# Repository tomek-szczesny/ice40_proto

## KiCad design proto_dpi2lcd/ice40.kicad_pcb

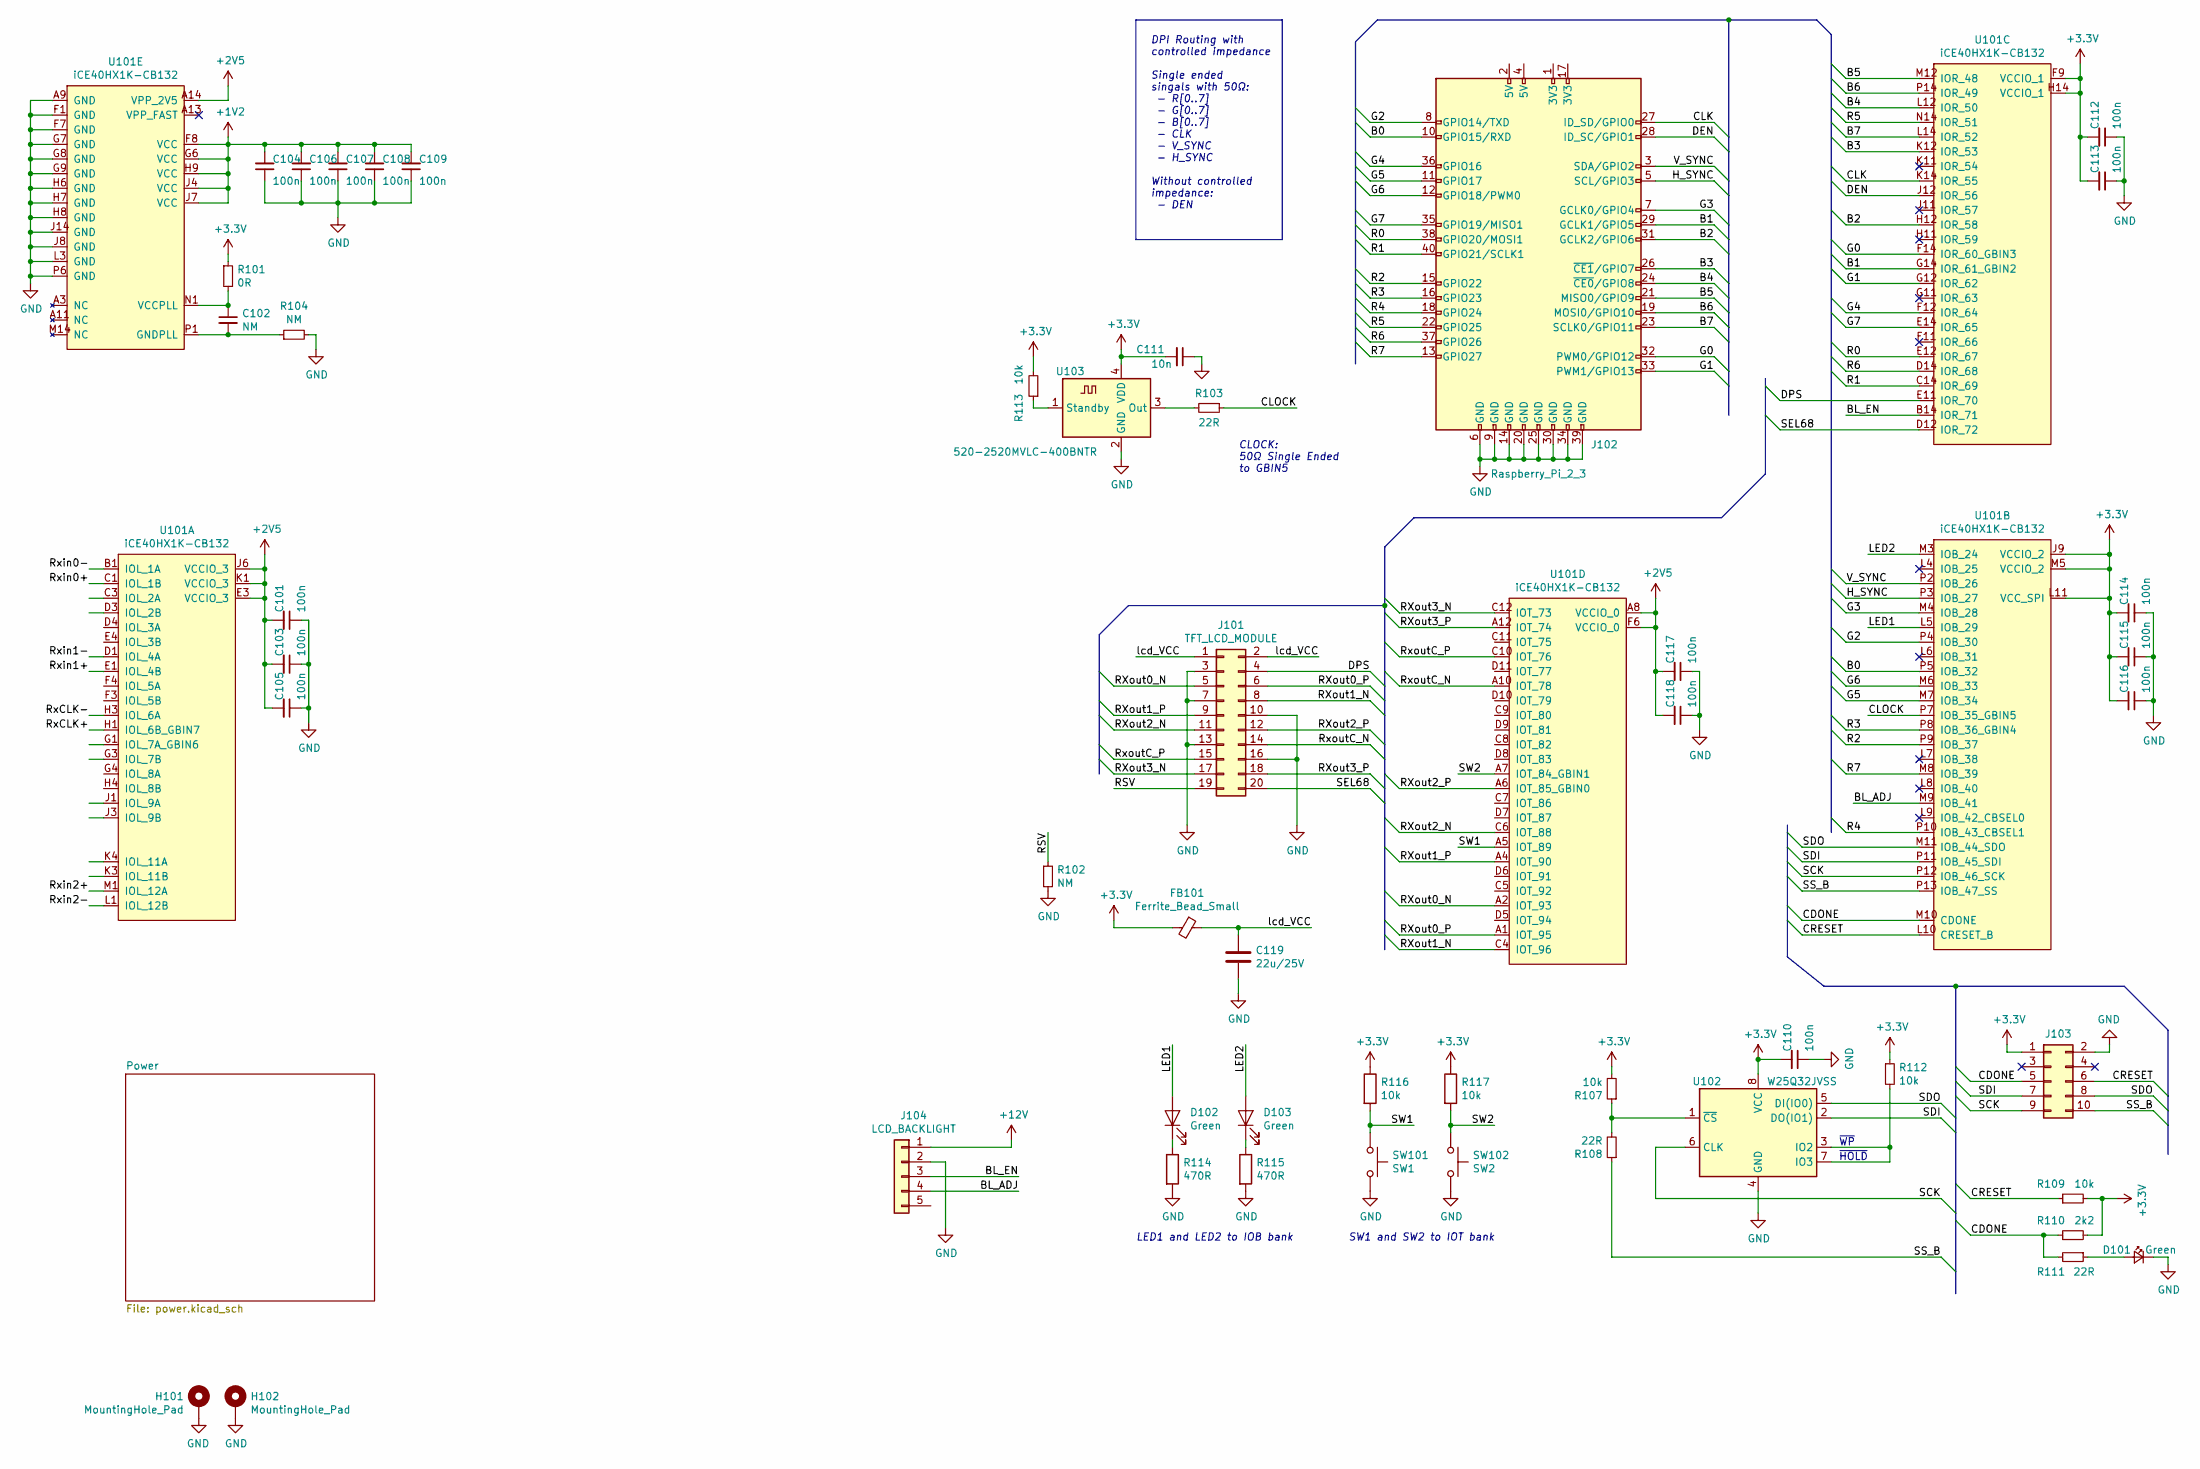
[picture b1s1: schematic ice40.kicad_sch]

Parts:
C101, C103, C104, C105, C106, C107, C108, C109: 100n; C_0402_1005Metric
C102: NM; C_0603_1608Metric
C110, C112, C113, C114, C115, C116, C117, C118: 100n; C_0603_1608Metric
C111: 10n; C_0603_1608Metric
C119: 22u/25V; C_1210_3225Metric
D101: Green; LED_0603_1608Metric
D102, D103: Green; D_0805_2012Metric
FB101: Ferrite_Bead_Small; L_1210_3225Metric_Pad1.42x2.65mm_HandSolder
H101, H102: MountingHole_Pad; MountingHole_3.2mm_M3_Pad_Via
J101: TFT_LCD_MODULE; IDC-Header_2x10_P2.54mm_Vertical
J102: Raspberry_Pi_2_3; IDC-Header_2x20_P2.54mm_Vertical
J103: Conn_02x05_Odd_Even; PinSocket_2x05_P2.54mm_Vertical
J104: LCD_BACKLIGHT; PinHeader_1x05_P2.54mm_Vertical
R101: 0R; R_0603_1608Metric
R102, R104: NM; R_0603_1608Metric
R103, R108, R111: 22R; R_0603_1608Metric
R107, R109, R112, R113, R116, R117: 10k; R_0603_1608Metric
R110: 2k2; R_0603_1608Metric
R114, R115: 470R; R_0603_1608Metric
SW101: SW1; SW_PUSH_6mm_H4.3mm
SW102: SW2; SW_PUSH_6mm_H4.3mm
U101: iCE40HX1K-CB132; Lattice_csBGA-132_Option2
U102: W25Q32JVSS; SOIC-8_5.23x5.23mm_P1.27mm
U103: 520-2520MVLC-400BNTR; Oscillator_SMD_Abracon_ASDMB-4Pin_2.5x2.0mm

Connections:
+1V2: C104.2, C106.2, C107.2, C108.2, C109.2, U101.F8 (VCC), U101.G6 (VCC), U101.H9 (VCC), U101.J4 (VCC), U101.J7 (VCC); also elsewhere on the board
+2V5: C101.2, C103.2, C105.2, C117.2, C118.2, U101.A8 (VCCIO_0), U101.A14 (VPP_2V5), U101.E3 (VCCIO_3), U101.F6 (VCCIO_0), U101.J6 (VCCIO_3), U101.K1 (VCCIO_3); also elsewhere on the board
+3V3: C110.2, C111.2, C112.2, C113.2, C114.2, C115.2, C116.2, FB101.2, J103.1, R101.1, R107.2, R109.2, R110.2, R112.1, R113.2, R116.1, R117.1, U101.F9 (VCCIO_1), U101.H14 (VCCIO_1), U101.J9 (VCCIO_2), U101.L11 (VCC_SPI), U101.M5 (VCCIO_2), U102.8 (VCC), U103.4 (VDD); also elsewhere on the board
+12V: J104.1; also elsewhere on the board
/B0: J102.10 (GPIO15/RXD), U101.P5 (IOB_32)
/B1: J102.29 (GCLK1/GPIO5), U101.G14 (IOR_61_GBIN2)
/B2: J102.31 (GCLK2/GPIO6), U101.H12 (IOR_58)
/B3: J102.26 (~CE1/GPIO7), U101.K12 (IOR_53)
/B4: J102.24 (~CE0/GPIO8), U101.L12 (IOR_50)
/B5: J102.21 (MISO0/GPIO9), U101.M12 (IOR_48)
/B6: J102.19 (MOSI0/GPIO10), U101.P14 (IOR_49)
/B7: J102.23 (SCLK0/GPIO11), U101.L14 (IOR_52)
/BL_ADJ: J104.4, U101.M9 (IOB_41)
/BL_EN: J104.3, U101.B14 (IOR_71)
/CDONE: J103.5, R110.1, R111.2, U101.M10 (CDONE)
/CLK: J102.27 (ID_SD/GPIO0), U101.K14 (IOR_55)
/CLOCK: R103.1, U101.P7 (IOB_35_GBIN5)
/CRESET: J103.6, R109.1, U101.L10 (CRESET_B)
/DEN: J102.28 (ID_SC/GPIO1), U101.J12 (IOR_56)
/DPS: J101.4, U101.E11 (IOR_70)
/G0: J102.32 (PWM0/GPIO12), U101.F14 (IOR_60_GBIN3)
/G1: J102.33 (PWM1/GPIO13), U101.G12 (IOR_62)
/G2: J102.8 (GPIO14/TXD), U101.P4 (IOB_30)
/G3: J102.7 (GCLK0/GPIO4), U101.M4 (IOB_28)
/G4: J102.36 (GPIO16), U101.F12 (IOR_64)
/G5: J102.11 (GPIO17), U101.M7 (IOB_34)
/G6: J102.12 (GPIO18/PWM0), U101.M6 (IOB_33)
/G7: J102.35 (GPIO19/MISO1), U101.E14 (IOR_65)
/H_SYNC: J102.5 (SCL/GPIO3), U101.P3 (IOB_27)
/LED1: D102.2 (A), U101.L5 (IOB_29)
/LED2: D103.2 (A), U101.M3 (IOB_24)
/R0: J102.38 (GPIO20/MOSI1), U101.E12 (IOR_67)
/R1: J102.40 (GPIO21/SCLK1), U101.C14 (IOR_69)
/R2: J102.15 (GPIO22), U101.P9 (IOB_37)
/R3: J102.16 (GPIO23), U101.P8 (IOB_36_GBIN4)
/R4: J102.18 (GPIO24), U101.P10 (IOB_43_CBSEL1)
/R5: J102.22 (GPIO25), U101.N14 (IOR_51)
/R6: J102.37 (GPIO26), U101.D14 (IOR_68)
/R7: J102.13 (GPIO27), U101.M8 (IOB_39)
/RSV: J101.19, R102.1
/RXout0_N: J101.5, U101.A2 (IOT_93)
/RXout0_P: J101.6, U101.A1 (IOT_95)
/RXout1_N: J101.8, U101.C4 (IOT_96)
/RXout1_P: J101.9, U101.A4 (IOT_90)
/RXout2_N: J101.11, U101.C6 (IOT_88)
/RXout2_P: J101.12, U101.A6 (IOT_85_GBIN0)
/RXout3_N: J101.17, U101.C12 (IOT_73)
/RXout3_P: J101.18, U101.A12 (IOT_74)
/RxCLK+: U101.H1 (IOL_6B_GBIN7)
/RxCLK-: U101.H3 (IOL_6A)
/Rxin0+: U101.C1 (IOL_1B)
/Rxin0-: U101.B1 (IOL_1A)
/Rxin1+: U101.E1 (IOL_4B)
/Rxin1-: U101.D1 (IOL_4A)
/Rxin2+: U101.M1 (IOL_12A)
/Rxin2-: U101.L1 (IOL_12B)
/RxoutC_N: J101.14, U101.A10 (IOT_78)
/RxoutC_P: J101.15, U101.C10 (IOT_76)
/SCK: J103.9, U101.P12 (IOB_46_SCK), U102.6 (CLK)
/SDI: J103.7, U101.P11 (IOB_45_SDI), U102.2 (DO(IO1))
/SDO: J103.8, U101.M11 (IOB_44_SDO), U102.5 (DI(IO0))
/SEL68: J101.20, U101.D12 (IOR_72)
/SS_B: J103.10, R108.1, U101.P13 (IOB_47_SS)
/SW1: R116.2, SW101.1, U101.A5 (IOT_89)
/SW2: R117.2, SW102.1, U101.A7 (IOT_84_GBIN1)
/V_SYNC: J102.3 (SDA/GPIO2), U101.P2 (IOB_26)
/lcd_VCC: C119.1, FB101.1, J101.1, J101.2
unnamed: C102.1, R101.2, U101.N1 (VCCPLL)
unnamed: C102.2, R104.1, U101.P1 (GNDPLL)
unnamed: D101.2 (A), R111.1
unnamed: D102.1 (K), R114.1
unnamed: D103.1 (K), R115.1
unnamed: R103.2, U103.3 (Out)
unnamed: R107.1, R108.2, U102.1 (~CS)
unnamed: R112.2, U102.3 (IO2), U102.7 (IO3)
unnamed: R113.1, U103.1 (Standby)

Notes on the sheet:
~{HOLD}
~{WP}
LED1 and LED2 to IOB bank
SW1 and SW2 to IOT bank
CLOCK: 50Ω Single Ended to GBIN5
DPI Routing with controlled impedance Single ended singals with 50Ω: - R[0..7] - G[0..7] - B[0..7] - CLK - V_SYNC - H_SYNC Without controlled impedance: - DEN

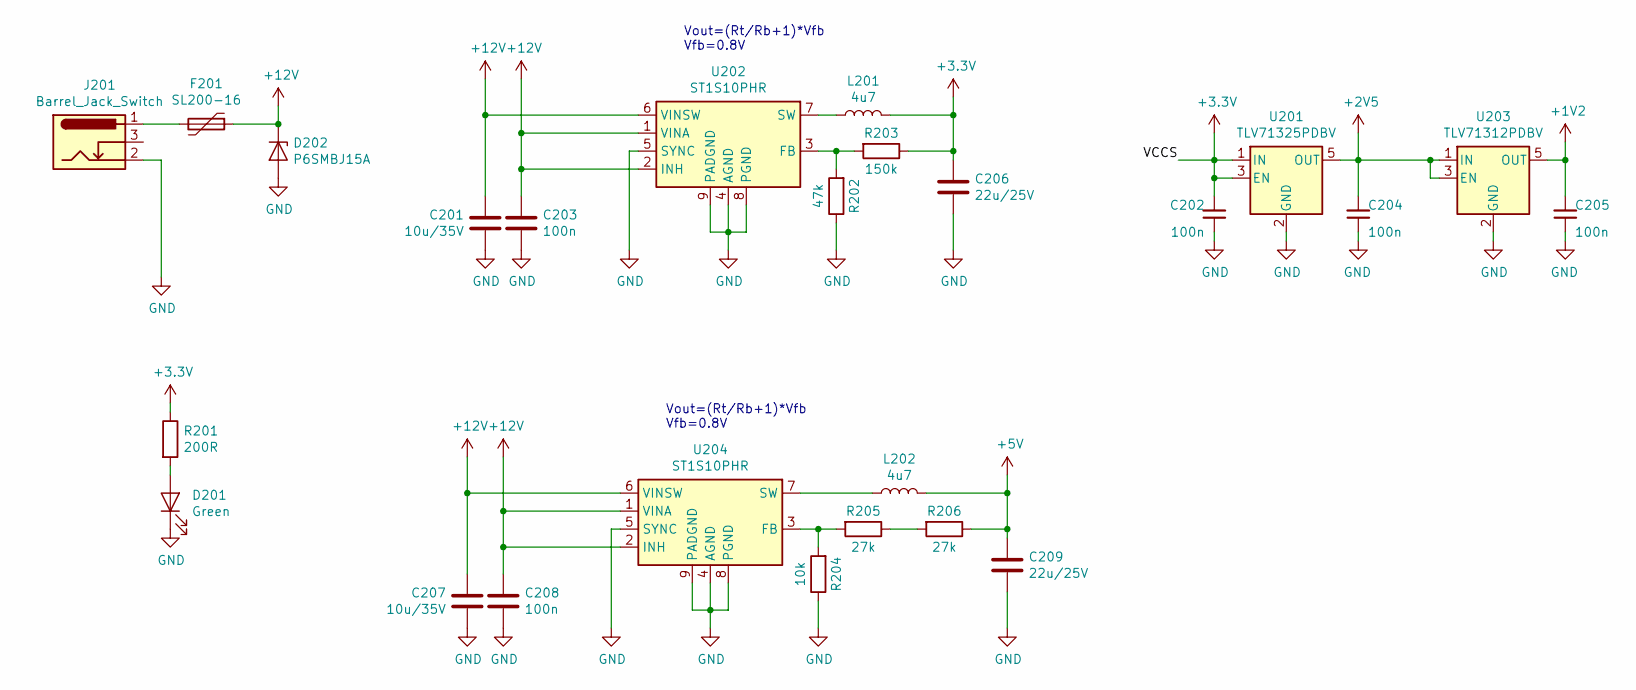
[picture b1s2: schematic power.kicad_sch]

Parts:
C201, C207: 10u/35V; C_1210_3225Metric
C202, C203, C204, C205, C208: 100n; C_0603_1608Metric
C206, C209: 22u/25V; C_1210_3225Metric
D201: Green; D_0805_2012Metric
D202: P6SMBJ15A; D_SMB
F201: SL200-16; Fuse_2920_7451Metric_Pad2.10x5.45mm_HandSolder
J201: Barrel_Jack_Switch; BarrelJack_Horizontal
L201, L202: 4u7; L_12x12mm_H8mm
R201: 200R; R_0603_1608Metric
R202: 47k; R_0603_1608Metric
R203: 150k; R_0603_1608Metric
R204: 10k; R_0603_1608Metric
R205, R206: 27k; R_0603_1608Metric
U201: TLV71325PDBV; SOT-23-5
U202, U204: ST1S10PHR; TI_SO-PowerPAD-8
U203: TLV71312PDBV; SOT-23-5

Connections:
+1V2: C205.2, U203.5 (OUT); also elsewhere on the board
+2V5: C204.2, U201.5 (OUT), U203.1 (IN), U203.3 (EN); also elsewhere on the board
+3V3: C202.2, C206.1, L201.2, R201.1, R203.1, U201.1 (IN), U201.3 (EN); also elsewhere on the board
+5V: C209.1, L202.2, R206.1
+12V: C201.2, C203.1, C207.2, C208.1, D202.1 (K), F201.1, U202.1 (VINA), U202.2 (INH), U202.6 (VINSW), U204.1 (VINA), U204.2 (INH), U204.6 (VINSW); also elsewhere on the board
unnamed: D201.2 (A), R201.2
unnamed: F201.2, J201.1
unnamed: L201.1, U202.7 (SW)
unnamed: L202.1, U204.7 (SW)
unnamed: R202.2, R203.2, U202.3 (FB)
unnamed: R204.2, R205.2, U204.3 (FB)
unnamed: R205.1, R206.2

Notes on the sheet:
Vout=(Rt/Rb+1)*Vfb Vfb=0.8V

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
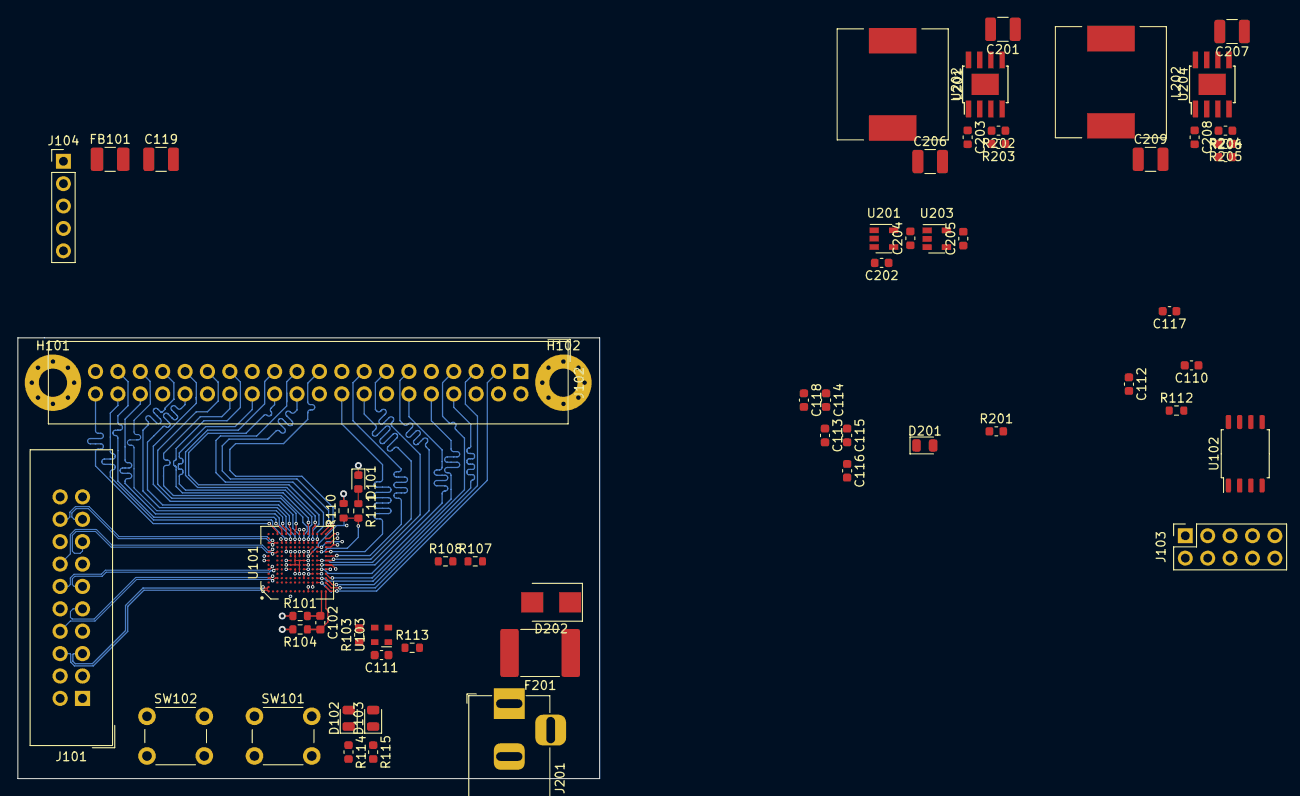
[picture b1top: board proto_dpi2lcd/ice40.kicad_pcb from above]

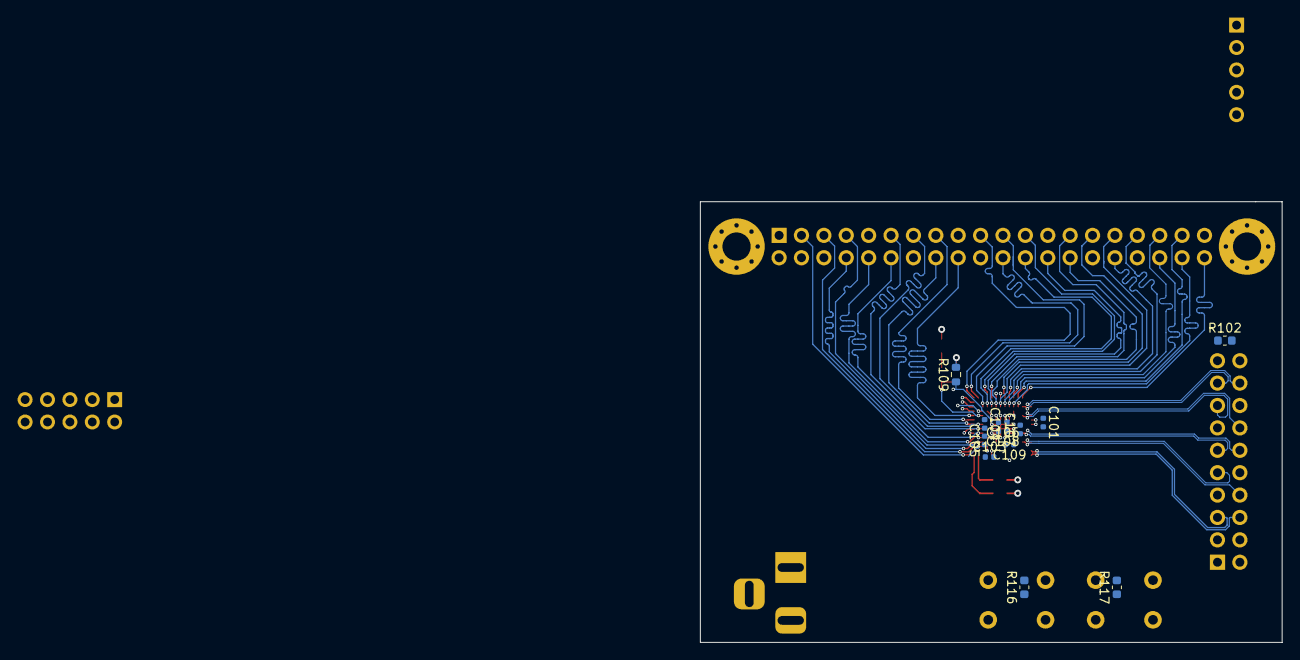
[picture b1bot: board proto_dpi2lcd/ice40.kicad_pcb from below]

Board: 4 copper layers, 66.0 x 50.0 mm, 74 parts (12 on the bottom side), 77 nets.

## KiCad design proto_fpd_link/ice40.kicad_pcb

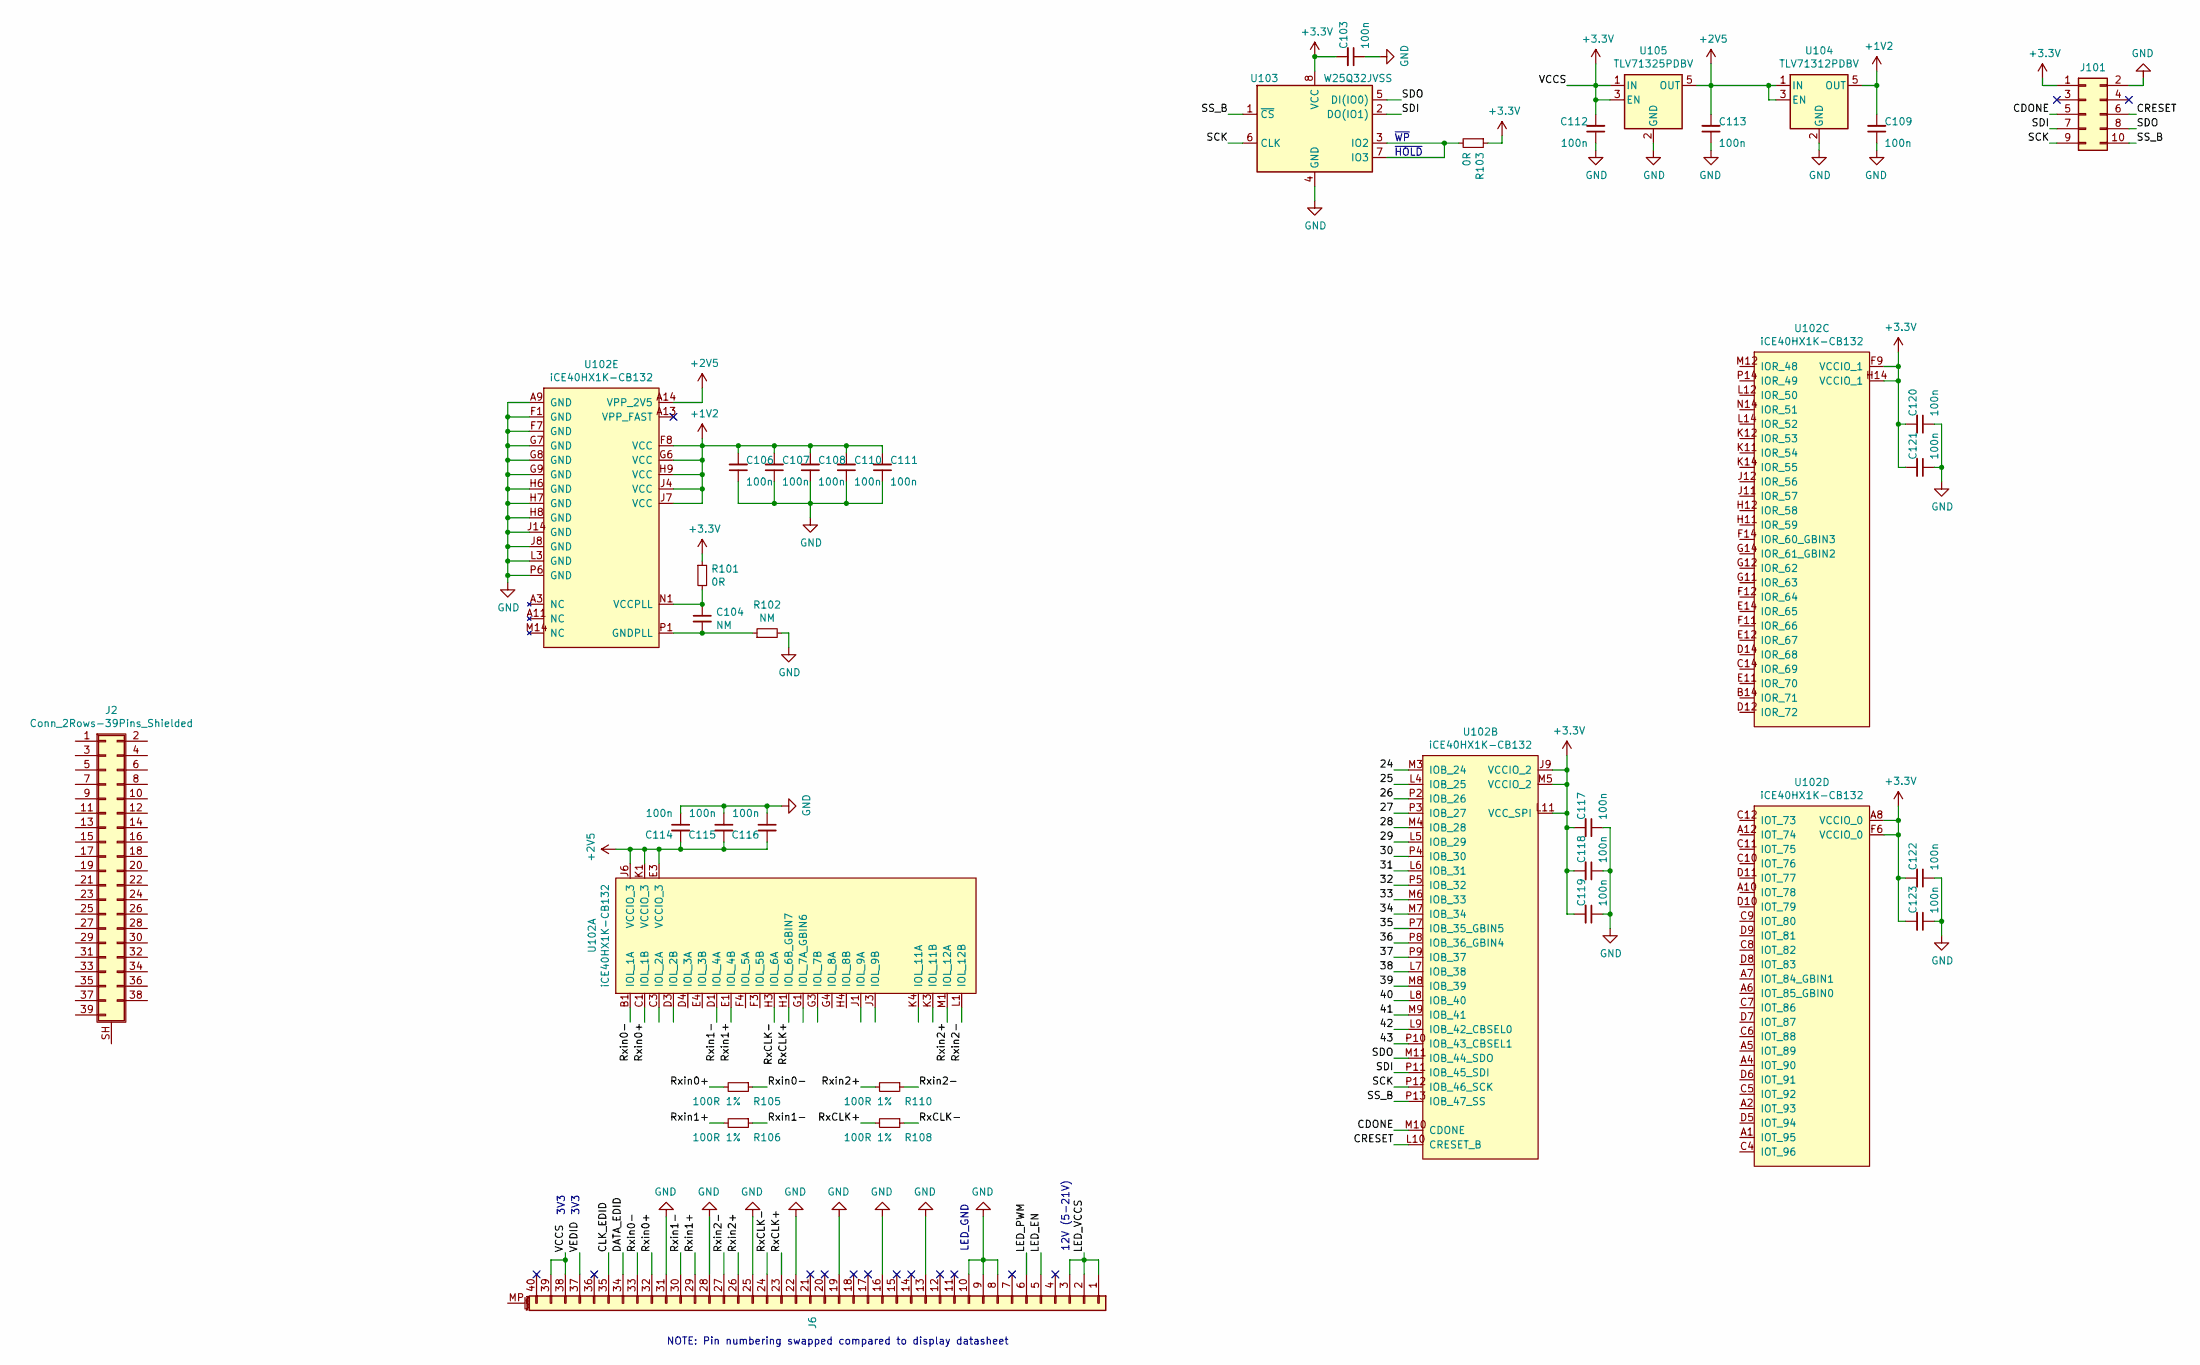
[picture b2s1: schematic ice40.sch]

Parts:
C103, C106, C107, C108, C109, C110, C111, C112, C113, C114, C115, C116, C117, C118, C119, C120, C121, C122, C123: 100n; C_0603_1608Metric
C104: NM; C_0603_1608Metric
J2: Conn_2Rows-39Pins_Shielded
J6: Conn_01x40_MountingPin; Hirose_FH12-40S-0.5SH_1x40-1MP_P0.50mm_Horizontal
J101: Conn_02x05_Odd_Even; PinSocket_2x05_P2.54mm_Vertical
R101, R103: 0R; R_0603_1608Metric
R102: NM; R_0603_1608Metric
R105, R106, R108, R110: 100R 1%; R_0402_1005Metric
U102: iCE40HX1K-CB132; Lattice_csBGA-132_Option2
U103: W25Q32JVSS; SOIC-8_5.23x5.23mm_P1.27mm
U104: TLV71312PDBV; SOT-23-5
U105: TLV71325PDBV; SOT-23-5

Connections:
+1V2: C106.2, C107.2, C108.2, C109.2, C110.2, C111.2, U102.F8 (VCC), U102.G6 (VCC), U102.H9 (VCC), U102.J4 (VCC), U102.J7 (VCC), U104.5 (OUT)
+2V5: C113.2, C114.2, C115.2, C116.2, U102.A14 (VPP_2V5), U102.E3 (VCCIO_3), U102.J6 (VCCIO_3), U102.K1 (VCCIO_3), U104.1 (IN), U104.3 (EN), U105.5 (OUT)
+3V3: C103.2, C112.2, C117.2, C118.2, C119.2, C120.2, C121.2, C122.2, C123.2, J6.38, J6.39, J101.1, R101.1, R103.1, U102.A8 (VCCIO_0), U102.F6 (VCCIO_0), U102.F9 (VCCIO_1), U102.H14 (VCCIO_1), U102.J9 (VCCIO_2), U102.L11 (VCC_SPI), U102.M5 (VCCIO_2), U103.8 (VCC), U105.1 (IN), U105.3 (EN)
/24: U102.M3 (IOB_24)
/25: U102.L4 (IOB_25)
/26: U102.P2 (IOB_26)
/27: U102.P3 (IOB_27)
/28: U102.M4 (IOB_28)
/29: U102.L5 (IOB_29)
/30: U102.P4 (IOB_30)
/31: U102.L6 (IOB_31)
/32: U102.P5 (IOB_32)
/33: U102.M6 (IOB_33)
/34: U102.M7 (IOB_34)
/35: U102.P7 (IOB_35_GBIN5)
/36: U102.P8 (IOB_36_GBIN4)
/37: U102.P9 (IOB_37)
/38: U102.L7 (IOB_38)
/39: U102.M8 (IOB_39)
/40: U102.L8 (IOB_40)
/41: U102.M9 (IOB_41)
/42: U102.L9 (IOB_42_CBSEL0)
/43: U102.P10 (IOB_43_CBSEL1)
/CDONE: J101.5, U102.M10 (CDONE)
/CLK_EDID: J6.35
/CRESET: J101.6, U102.L10 (CRESET_B)
/DATA_EDID: J6.34
/LED_EN: J6.5
/LED_PWM: J6.6
/LED_VCCS: J6.1, J6.2, J6.3
/RxCLK+: J6.23, R108.2, U102.H1 (IOL_6B_GBIN7)
/RxCLK-: J6.24, R108.1, U102.H3 (IOL_6A)
/Rxin0+: J6.32, R105.2, U102.C1 (IOL_1B)
/Rxin0-: J6.33, R105.1, U102.B1 (IOL_1A)
/Rxin1+: J6.29, R106.2, U102.E1 (IOL_4B)
/Rxin1-: J6.30, R106.1, U102.D1 (IOL_4A)
/Rxin2+: J6.26, R110.2, U102.M1 (IOL_12A)
/Rxin2-: J6.27, R110.1, U102.L1 (IOL_12B)
/SCK: J101.9, U102.P12 (IOB_46_SCK), U103.6 (CLK)
/SDI: J101.7, U102.P11 (IOB_45_SDI), U103.2 (DO(IO1))
/SDO: J101.8, U102.M11 (IOB_44_SDO), U103.5 (DI(IO0))
/SS_B: J101.10, U102.P13 (IOB_47_SS), U103.1 (~CS)
/VEDID: J6.37
GND: C103.1, C106.1, C107.1, C108.1, C109.1, C110.1, C111.1, C112.1, C113.1, C114.1, C115.1, C116.1, C117.1, C118.1, C119.1, C120.1, C121.1, C122.1, C123.1, J6.8, J6.9, J6.10, J6.13, J6.16, J6.19, J6.22, J6.25, J6.28, J6.31, J101.2, R102.2, U102.A9 (GND), U102.F1 (GND), U102.F7 (GND), U102.G7 (GND), U102.G8 (GND), U102.G9 (GND), U102.H6 (GND), U102.H7 (GND), U102.H8 (GND), U102.J8 (GND), U102.J14 (GND), U102.L3 (GND), U102.P6 (GND), U103.4 (GND), U104.2 (GND), U105.2 (GND)
unnamed: C104.1, R101.2, U102.N1 (VCCPLL)
unnamed: C104.2, R102.1, U102.P1 (GNDPLL)
unnamed: R103.2, U103.3 (IO2), U103.7 (IO3)

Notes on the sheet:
~WP
~HOLD
LED_GND
3V3
12V (5-21V)
NOTE: Pin numbering swapped compared to display datasheet

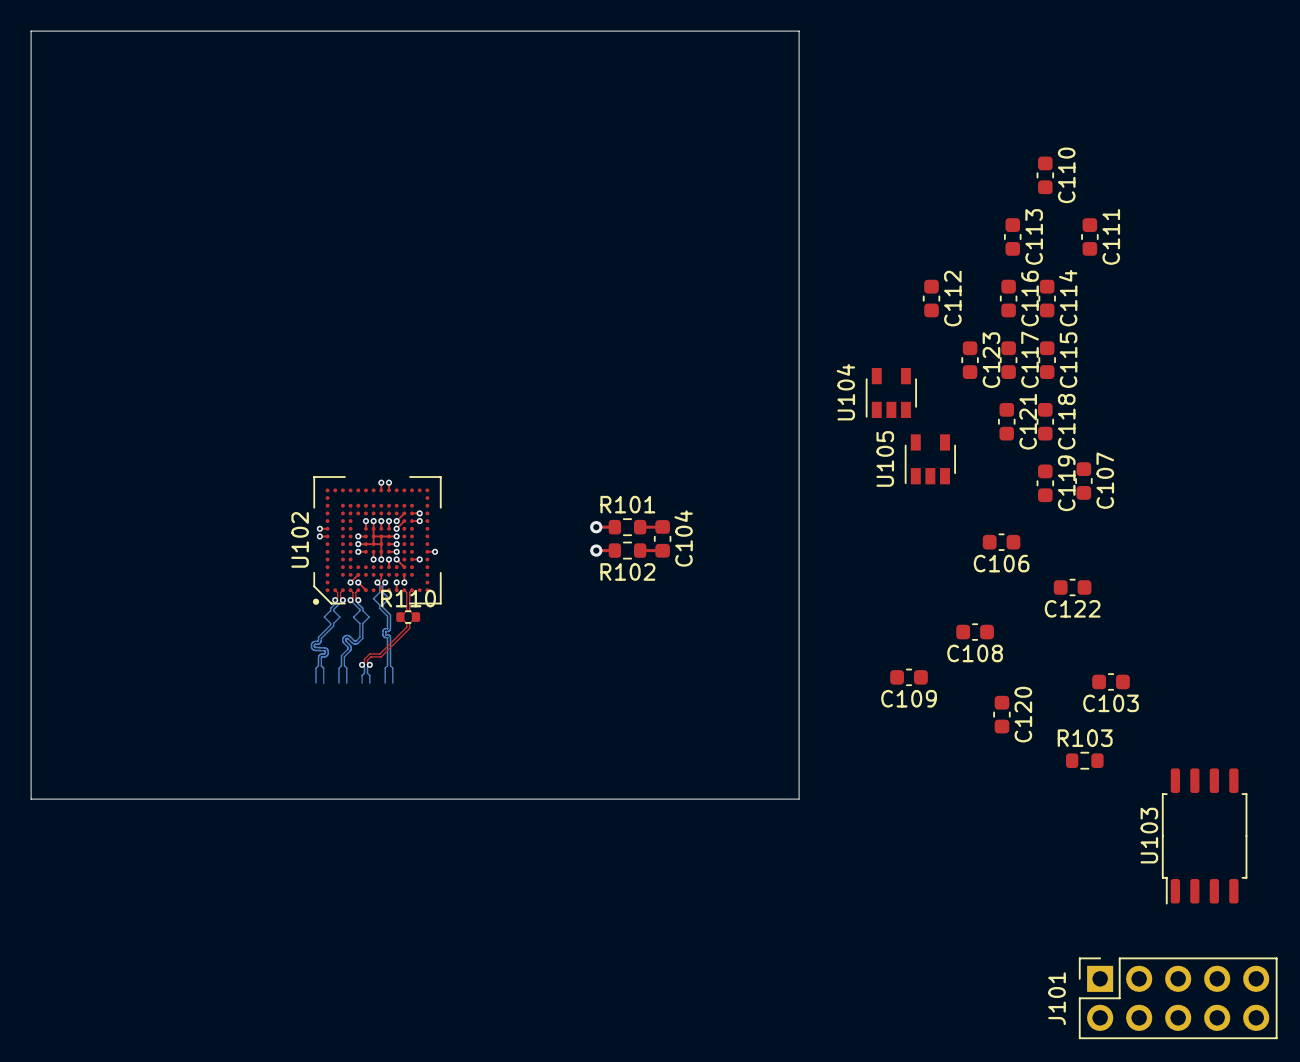
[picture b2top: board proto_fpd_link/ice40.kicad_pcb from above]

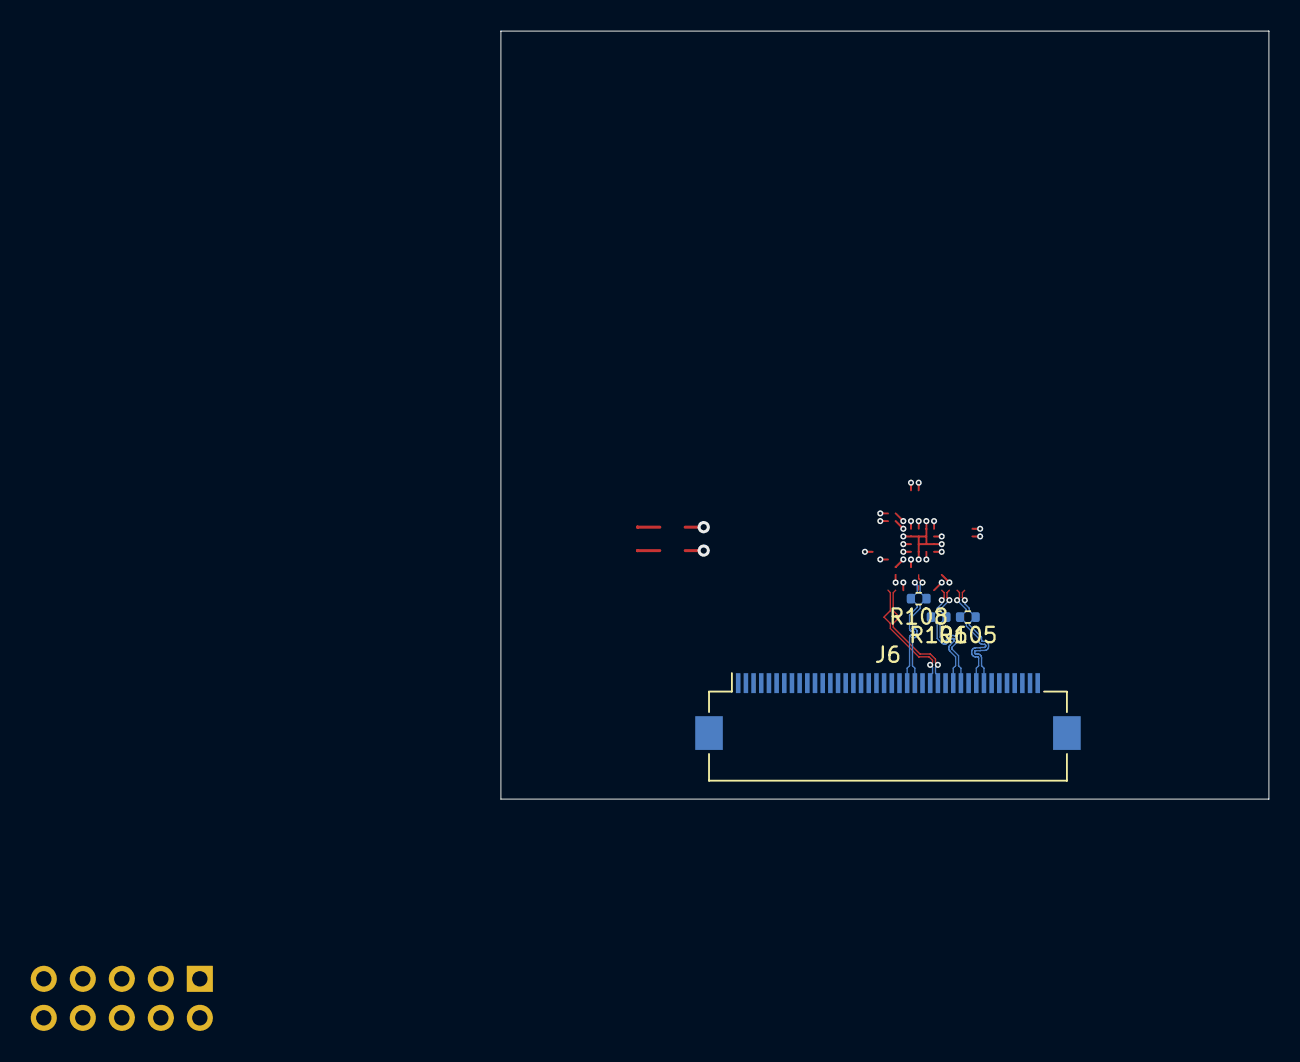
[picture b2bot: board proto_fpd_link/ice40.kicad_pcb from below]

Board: 4 copper layers, 50.0 x 50.0 mm, 33 parts (4 on the bottom side), 22 nets.

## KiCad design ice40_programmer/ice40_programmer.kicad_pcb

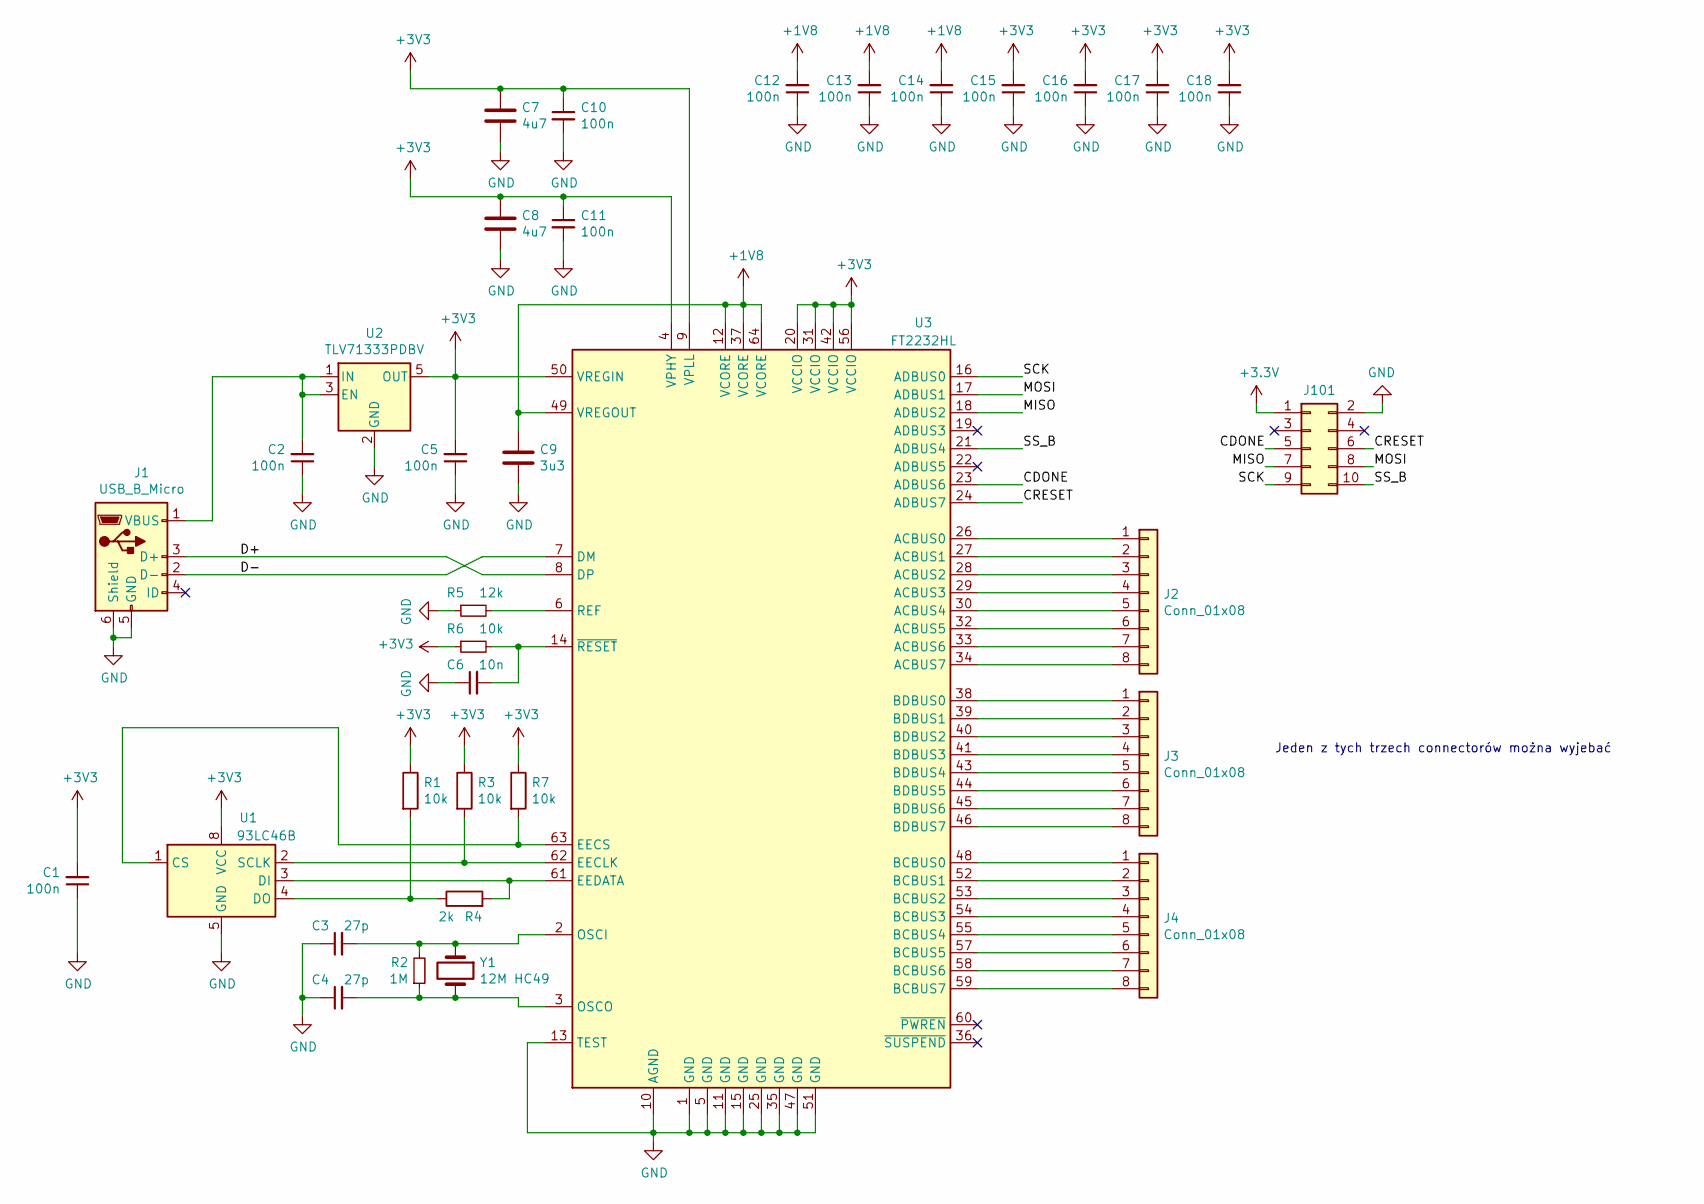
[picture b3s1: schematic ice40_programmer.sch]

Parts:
C1, C2, C5, C10, C11, C12, C13, C14, C15, C16, C17, C18: 100n; C_0603_1608Metric
C3, C4: 27p; C_0603_1608Metric
C6: 10n; C_0603_1608Metric
C7, C8: 4u7; C_0603_1608Metric
C9: 3u3; C_0603_1608Metric
J1: USB_B_Micro; USB_Micro-AB_Molex_47590-0001
J2, J3, J4: Conn_01x08; PinHeader_1x08_P2.54mm_Vertical
J101: Conn_02x05_Odd_Even; PinSocket_2x05_P2.54mm_Vertical
R1, R3, R6, R7: 10k; R_0603_1608Metric
R2: 1M; R_0603_1608Metric
R4: 2k; R_0603_1608Metric
R5: 12k; R_0603_1608Metric
U1: 93LC46B; SOIC-8_3.9x4.9mm_P1.27mm
U2: TLV71333PDBV; SOT-23-5
U3: FT2232HL; LQFP-64_10x10mm_P0.5mm
Y1: 12M HC49; Crystal_SMD_HC49-SD

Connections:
+1V8: C9.1, C12.2, C13.2, C14.2, U3.12 (VCORE), U3.37 (VCORE), U3.49 (VREGOUT), U3.64 (VCORE)
/CDONE: J101.5, U3.23 (ADBUS6)
/CRESET: J101.6, U3.24 (ADBUS7)
/D+: J1.3 (D+), U3.8 (DP)
/D-: J1.2 (D-), U3.7 (DM)
/MISO: J101.7, U3.18 (ADBUS2)
/MOSI: J101.8, U3.17 (ADBUS1)
/SCK: J101.9, U3.16 (ADBUS0)
/SS_B: J101.10, U3.21 (ADBUS4)
GND: C1.1, C2.1, C3.1, C4.1, C5.1, C6.1, C7.2, C8.2, C9.2, C10.2, C11.2, C12.1, C13.1, C14.1, C15.1, C16.1, C17.1, C18.1, J1.5 (GND), J1.6 (Shield), J101.2, R5.1, U1.5 (GND), U2.2 (GND), U3.1 (GND), U3.5 (GND), U3.10 (AGND), U3.11 (GND), U3.13 (TEST), U3.15 (GND), U3.25 (GND), U3.35 (GND), U3.47 (GND), U3.51 (GND)
unnamed: C2.2, J1.1 (VBUS), U2.1 (IN), U2.3 (EN)
unnamed: C3.2, R2.2, U3.2 (OSCI), Y1.1
unnamed: C4.2, R2.1, U3.3 (OSCO), Y1.2
unnamed: C6.2, R6.2, U3.14 (~RESET)
unnamed: J2.1, U3.26 (ACBUS0)
unnamed: J2.2, U3.27 (ACBUS1)
unnamed: J2.3, U3.28 (ACBUS2)
unnamed: J2.4, U3.29 (ACBUS3)
unnamed: J2.5, U3.30 (ACBUS4)
unnamed: J2.6, U3.32 (ACBUS5)
unnamed: J2.7, U3.33 (ACBUS6)
unnamed: J2.8, U3.34 (ACBUS7)
unnamed: J3.1, U3.38 (BDBUS0)
unnamed: J3.2, U3.39 (BDBUS1)
unnamed: J3.3, U3.40 (BDBUS2)
unnamed: J3.4, U3.41 (BDBUS3)
unnamed: J3.5, U3.43 (BDBUS4)
unnamed: J3.6, U3.44 (BDBUS5)
unnamed: J3.7, U3.45 (BDBUS6)
unnamed: J3.8, U3.46 (BDBUS7)
unnamed: J4.1, U3.48 (BCBUS0)
unnamed: J4.2, U3.52 (BCBUS1)
unnamed: J4.3, U3.53 (BCBUS2)
unnamed: J4.4, U3.54 (BCBUS3)
unnamed: J4.5, U3.55 (BCBUS4)
unnamed: J4.6, U3.57 (BCBUS5)
unnamed: J4.7, U3.58 (BCBUS6)
unnamed: J4.8, U3.59 (BCBUS7)
unnamed: R1.2, R4.1, U1.4 (DO)
unnamed: R3.2, U1.2 (SCLK), U3.62 (EECLK)
unnamed: R4.2, U1.3 (DI), U3.61 (EEDATA)
unnamed: R5.2, U3.6 (REF)
unnamed: R7.2, U1.1 (CS), U3.63 (EECS)

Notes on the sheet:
Jeden z tych trzech connectorów można wyjebać

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
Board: 2 copper layers, 34 parts (0 on the bottom side), 44 nets, no tracks yet.

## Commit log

2021-10-20 Moving one board into respective subdir
2021-10-20 initial commit of ice40 programmer board
2021-10-24 Adding new version of proto board
2021-10-24 Rename the second proto board, dedicated for DPI to LCD 10' chi-mei panel (LVDS)
2021-10-24 Added bom quickly
2021-10-25 Work in progress
    - Schematic of 12V to 3,3V BUCK
    - pin allocation from RPi header to FPGA
2021-10-25 Fanout of DPI
    (Display Parallel Interface)
2021-10-28 Progressing
2021-11-01 Progress
    Sheets work
    - almost all J101 singals connected with FPGA
    - Bank IOT connected to +2V5
    - bus added between J101 and FPGA
    - general sheet cleanup
    - LEDs and SWs connected to FPGA
2021-11-01 Added gitignore
2021-12-01 Work in progress
    - Added BUCK for 12V->5V but inductors are TBD
    - Progress to the layout
    - some pin swapping has been done
2021-12-03 1st routing of the rpi connector
2022-01-14 Routing progress
    - switched to KiCAD 6.0.0
    - defined stackup, according to JLC PCB inside the project PCB settings
    - fully routed FGPA to 40pin header, with track length tunned
    - routed diff-pairs of LVDSes from FPGA to the pin-header
2022-01-14 Ignore backup in the favor of the GIT
